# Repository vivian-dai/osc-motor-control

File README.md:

# osc-motor-control
code/firmware/electrical wiring diagrams for trying to get a motor to work through qlab network cues

## Hardware
The board is a ESP-WROOM-32, connect to uPesy ESP32 Wroom DevKit in the Arduino IDE

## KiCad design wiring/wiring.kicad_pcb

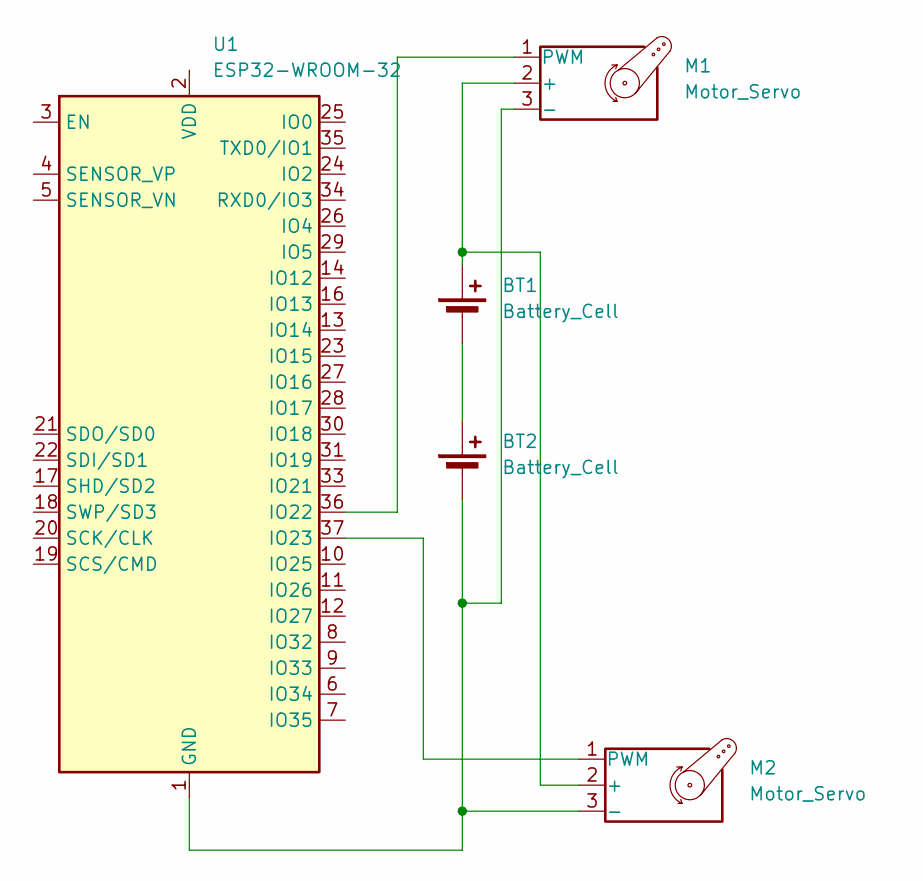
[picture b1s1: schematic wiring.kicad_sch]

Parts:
BT1, BT2: Battery_Cell; Wago_734-132_1x02_P3.50mm_Vertical
M1, M2: Motor_Servo; FanPinHeader_1x03_P2.54mm_Vertical
U1: ESP32-WROOM-32

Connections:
unnamed: BT1.1 (+), M1.2 (+), M2.2 (+)
unnamed: BT1.2 (-), BT2.1 (+)
unnamed: BT2.2 (-), M1.3 (-), M2.3 (-), U1.1 (GND), U1.15 (GND), U1.38 (GND), U1.39 (GND)
unnamed: M1.1 (PWM), U1.36 (IO22)
unnamed: M2.1 (PWM), U1.37 (IO23)

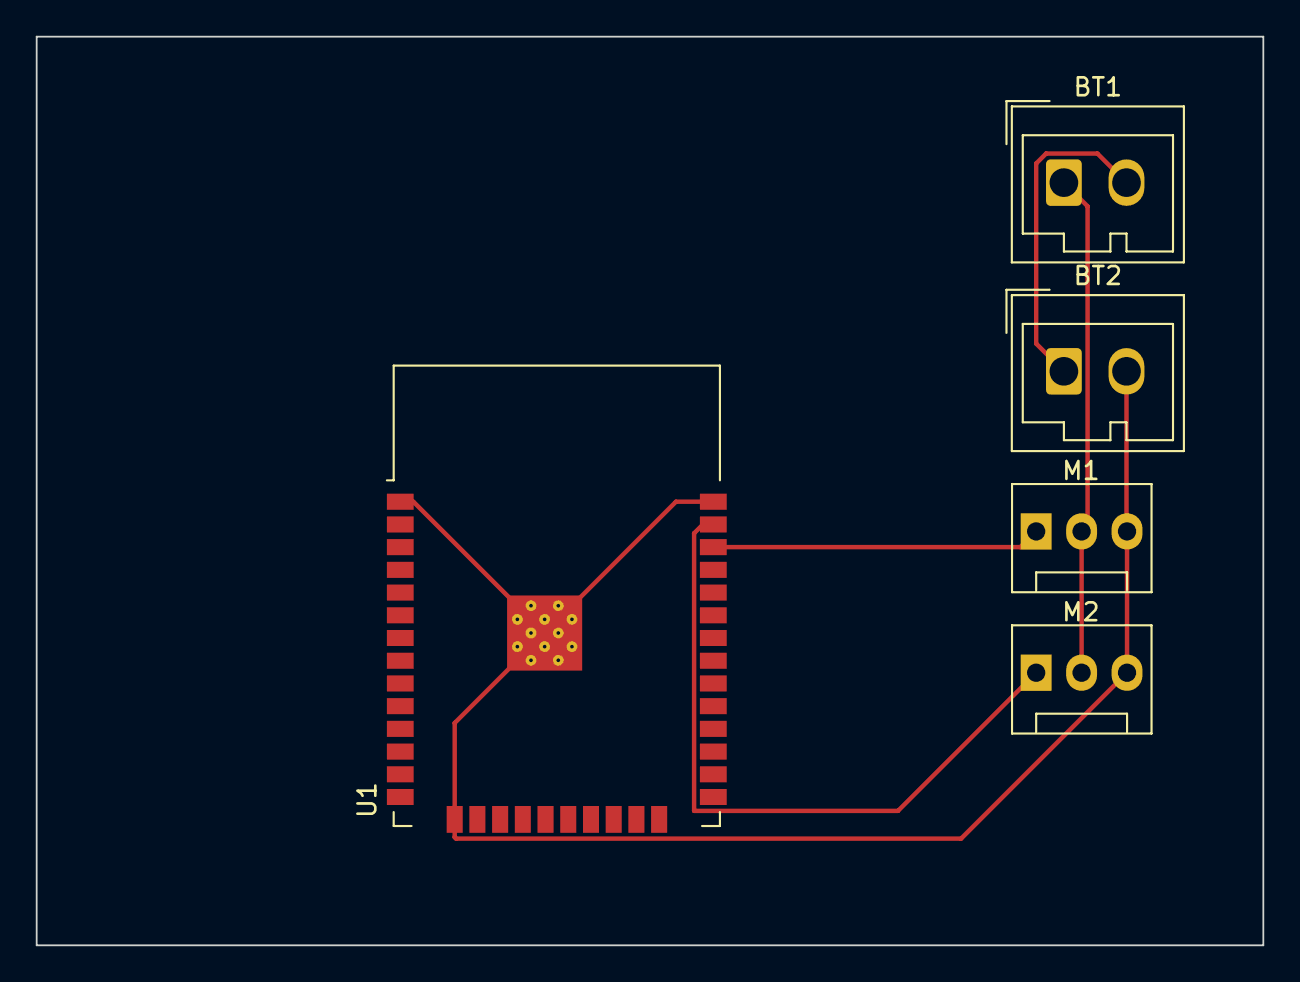
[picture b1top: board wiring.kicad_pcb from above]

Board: 2 copper layers, 68.6 x 50.8 mm, 5 parts (0 on the bottom side), 5 nets.

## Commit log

2025-10-13 initial wiring attempts
2025-10-18 server
2025-10-18 works on udp
2025-11-09 left right controls
